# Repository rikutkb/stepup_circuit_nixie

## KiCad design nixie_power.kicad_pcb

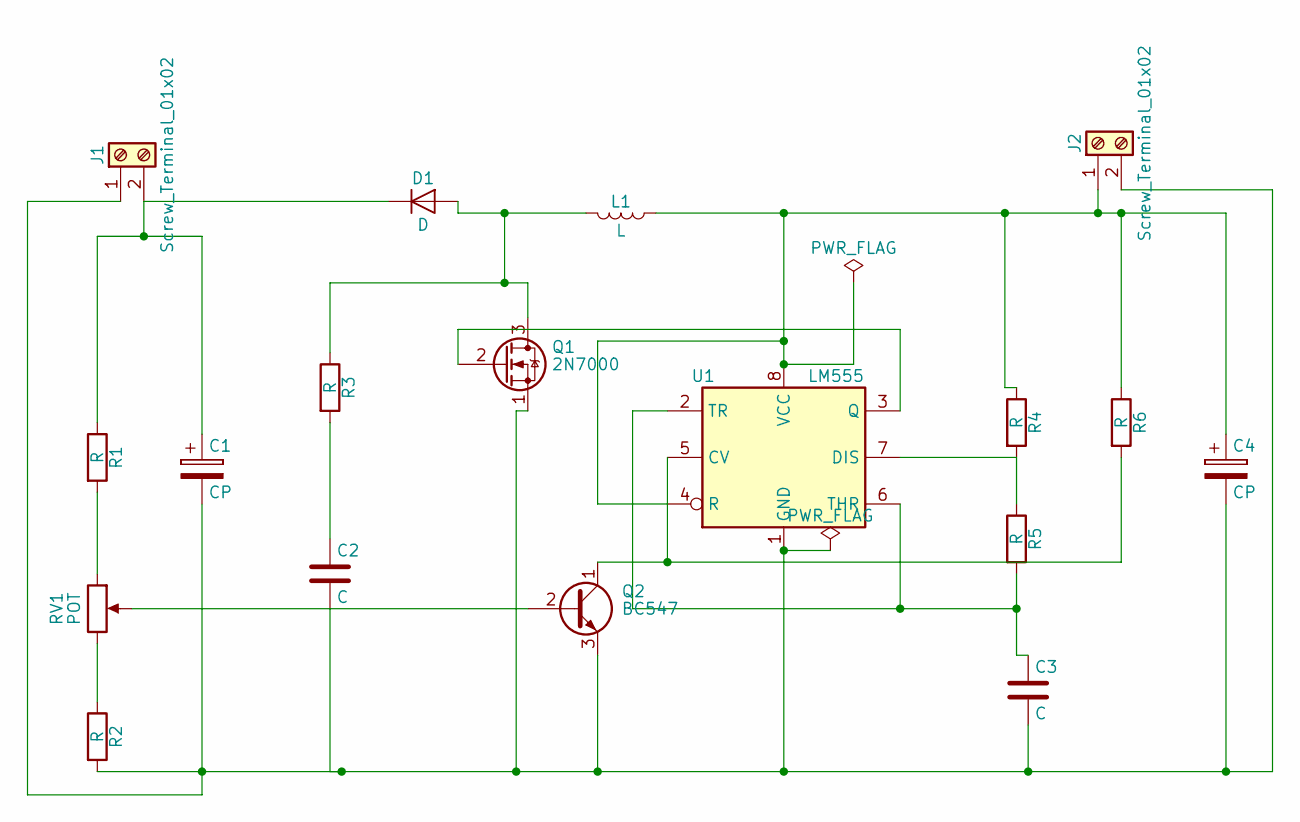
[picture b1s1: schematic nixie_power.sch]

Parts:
C1, C4: CP
C2, C3: C
D1: D
J1, J2: Screw_Terminal_01x02
L1: L
Q1: 2N7000; TO-92_Molded_Narrow
Q2: BC547; TO-92_Molded_Narrow
R1, R2, R3, R4, R5, R6: R
RV1: POT
U1: LM555

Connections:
unnamed: C1.1, D1.1 (K), J1.2, R1.1
unnamed: C1.2, C2.2, C3.2, C4.2, J1.1, J2.2, Q1.1 (S), Q2.3 (E), R2.2, U1.1 (GND)
unnamed: C2.1, R3.2
unnamed: C3.1, R5.2, U1.2 (TR), U1.6 (THR)
unnamed: C4.1, J2.1, L1.1, R4.1, R6.1, U1.4 (R), U1.8 (VCC)
unnamed: D1.2 (A), L1.2, Q1.3 (D), R3.1
unnamed: Q1.2 (G), U1.3 (Q)
unnamed: Q2.1 (C), R6.2, U1.5 (CV)
unnamed: Q2.2 (B), RV1.2
unnamed: R1.2, RV1.1
unnamed: R2.1, RV1.3
unnamed: R4.2, R5.1, U1.7 (DIS)

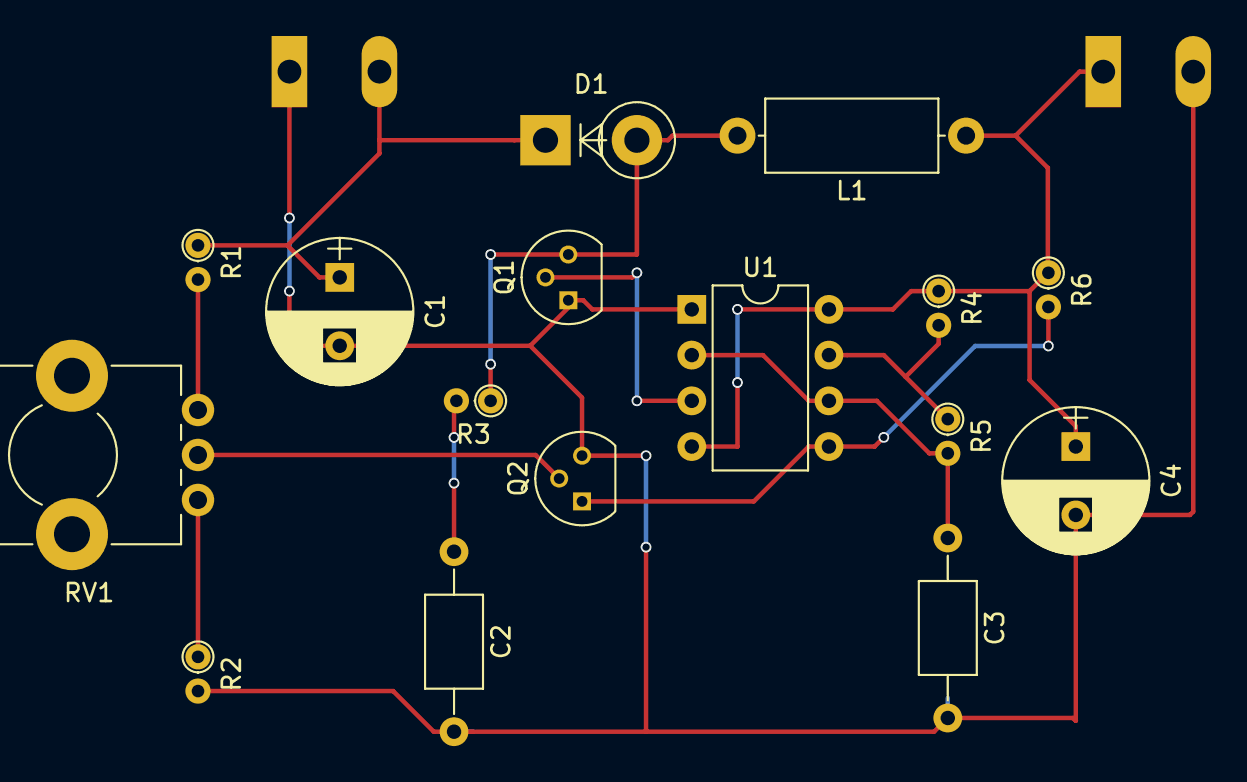
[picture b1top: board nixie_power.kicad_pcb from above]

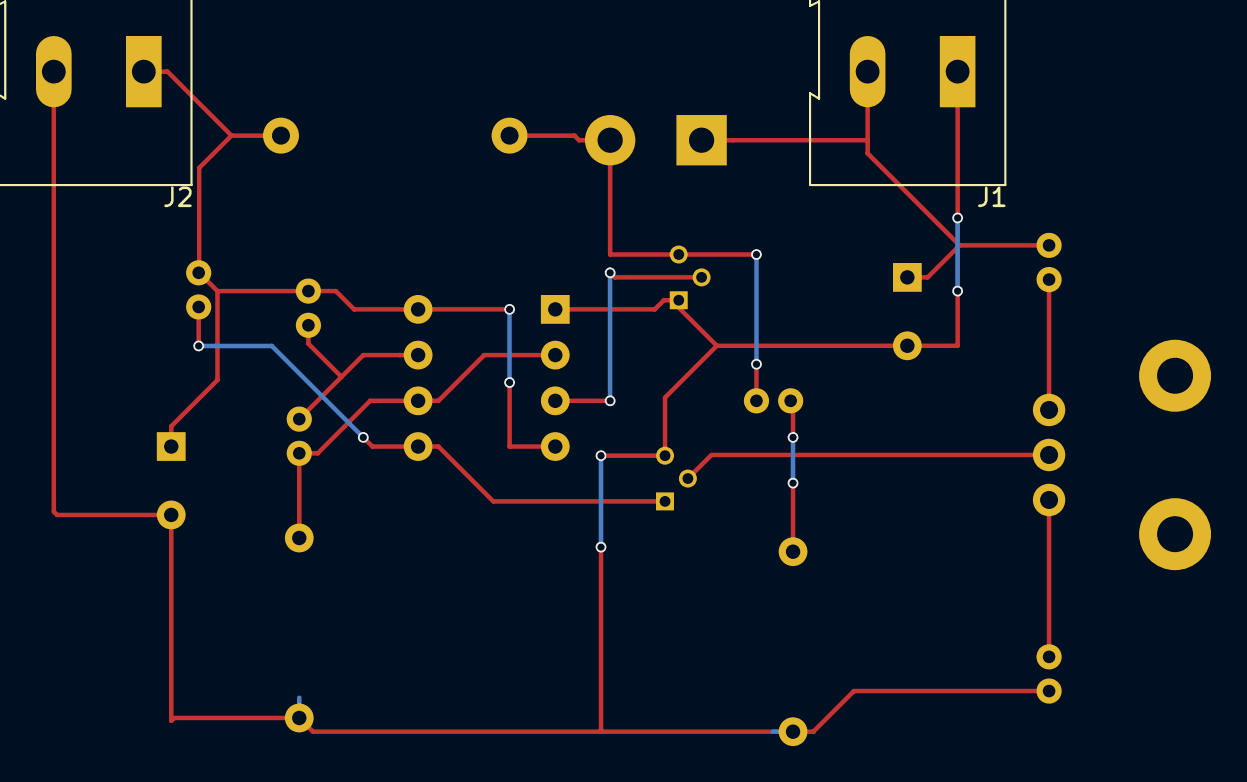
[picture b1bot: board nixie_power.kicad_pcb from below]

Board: 2 copper layers, 18 parts (2 on the bottom side), 12 nets.

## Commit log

2018-04-16 パーツ選び
    パーツを追加した
2018-04-16 配線をした
2018-04-16 オート配線をした
    これから手動配線でジャンパワイヤに変更する
2018-04-16 穴の開け方を変更した
